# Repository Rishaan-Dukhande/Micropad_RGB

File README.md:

# Rishaan RGB micro hackpad

The RGB micro is a 2 key macropad with a joystick, an OLED Display, and one RGB LED - giving the user multiple ways to change an LED to any color and brightness they want! This serves as the first PCB I have created and is a great introductory project to develop PCB, CAD, and firmware skills for engineering! I created this project to develop these skills and enhance my engineering skills and knowledge. I have used RGBs and there is a color game called hues and cues, and this LED allows you to access a pallet just like the game, but in real life! Features, Images, and steps to recreate this project are listed below.

# Demo

## Features:

* Portable 3D case with openings for components and USB connection
* Seeeduino XIAO SAMD21 controller
* 1 RGB LED for bright color display
* 2 tactile switch buttons for modes and presets
* Small OLED screen that displays the current RGB value in real time.
* Joystick for smooth & dynamic brightness and color control

## How it works

The RGB Micropad is a mini RGB LED controller. The joystick navigates 
a full 360° color wheel — pushing in any direction changes the LED to 
that hue in real time. SW1 toggles between Color mode and Brightness 
mode, while SW2 cycles through 8 color presets. Pressing the joystick 
button activates Saturation mode, letting the user dial between vivid 
and pastel tones and creating a larger array of colors for the LED to
display. The OLED screen shows the current mode, color name, 
RGB values, and brightness percentage at all times.

## PCB

Here's my PCB! Kicad was used to create both the schematic and layout of the pcb.

### Schematic

### PCB

The 1x4 connector on the top is for connecting the Oled Screen (SSD1306 0.91" OLED I2C 128x32) The 1x5 connector on the bottom center of the pcb is for connecting the controling joystick

## Sizes and PCB Info

* Board size: 56.95mm x 68.85mm
* 2 layer PCB
* Designed in KiCad 9.0

## Firmware
Written in CircuitPython. The main.py file enables the user to have the following controls:
* SW1 → Toggle between Color mode and Brightness mode
* SW2 → Cycle through 8 color presets
* Joystick button → Toggle saturation mode on/off
* Joystick X/Y → Navigate color wheel (Color mode) or adjust brightness (Brightness mode)
* OLED display → Shows current mode, color name, RGB values, and brightness %

## BOM:

Here is everything used in the RGB micro hackpad. Note that most of the prices come in sets because components cost the least when they are bought in bulk.

| **Qty** | **Component** | **Note** | **Price** |
|:--:|:--:|:--:|:--:|
| 1 | Seeeduino XIAO SAMD21 | Main processor | [~$5.40](https://www.seeedstudio.com/Seeeduino-XIAO-Arduino-Microcontroller-SAMD21-Cortex-M0+-p-4426.html) |
| 1 | SSD1306 0.91" OLED I2C 128x32 | Displays brightness and color info | [~$7.99](https://www.amazon.com/gp/product/B079BN2J8V/ref=ewc_pr_img_4?smid=A1WZRPJ0MN58A9&th=1) |
| 1 | Analog thumbstick joystick module KY-023 | Joystick control | [~$7.99](https://www.amazon.com/gp/product/B0GWQ6KXYP/ref=ewc_pr_img_3?smid=A3S807LE0L63AP&psc=1) |
| 1 | RGB LED 5mm common cathode | LED that is being controlled | [~$8.99 (100 pack)](https://www.amazon.com/gp/product/B01C3ZZT8W/ref=ewc_pr_img_1?smid=A14FP9XIRL6C1F&th=1) |
| 2 | 10KΩ resistor | Pull up resistors for buttons | [~$8.99 (kit)](https://www.amazon.com/Elegoo-Values-Resistor-Assortment-Compliant/dp/B072BL2VX1) |
| 1 | 220Ω resistor | Red LED pin | [included in resistor kit](https://www.amazon.com/Elegoo-Values-Resistor-Assortment-Compliant/dp/B072BL2VX1) |
| 2 | 47Ω resistor | Green and Blue LED pins | [included in resistor kit](https://www.amazon.com/Elegoo-Values-Resistor-Assortment-Compliant/dp/B072BL2VX1) |
| 2 | Tactile push button 6x6mm | Control modes for joystick control | [~$5.99 (pack)](https://www.amazon.com/gp/product/B07VSNN9S2/ref=ewc_pr_img_2?smid=AJJYA8M5YMCKV&psc=1) |
| 1 | 2.54mm pin header 1x04 | OLED screen connector | [~$6.99 (pack)](https://www.amazon.com/MCIGICM-Header-2-54mm-Arduino-Connector/dp/B07PKKY8BX) |
| 1 | 2.54mm pin header 1x05 | Joystick connector | [included in pack above](https://www.amazon.com/MCIGICM-Header-2-54mm-Arduino-Connector/dp/B07PKKY8BX) |

## Steps to Reproduce

### Parts
Order the parts in the Bill of Materials. These will be soldered on the PCB manually later on (unless specified in JLCPCB)

### PCB Manufacturing
1. Download PCB/gerbers.zip (in PCB folder of repository)
2. Upload to JLCPCB or PCBWay (You can get grants from hackclub if you edit the PCB before upload!)
3. Place the order - remember to pick the least expensive shipping!

### Assembly

1. Solder resistors R1-R5 onto the PCB. Utilize the following resistor values
2. Refer to the table above to read resistor values before incorporating them.
The table below has the resistor values with their placement on the PCB.

| **R#** | **Value** |
|:--:|:--:|
| R1 | 220Ω |
| R2 | 47Ω |
| R3 | 47Ω |
| R4 | 10KΩ |
| R5 | 10KΩ |
  
3. Solder RGB LED into the D1 slot on the PCB
4. Solder tactile switches SW1 and SW2.
5. Solder 5 pin header into the slot for the Joystick
6. Solder 4 pin header into the slot for the OLED screen
7. Solder XIAO SAMD21 on the top left of the board

### Flashing Instructions (Get firmware onto the PCB)
1. Copy or download the firmware as a .ino file and open it in arduino IDE
2. Use a USB-C transfer cable and plug it into the seedunio XAMD 21 and a computer
3. Upload the code using arduino IDE
4. The RGB Micropad will automatically begin to work (it can be plugged in directly to power)

### Verify your RGB Micropad works!
1. Plug in via USB (either computer of any electricity source)
2. OLED should show RGB Micropad splash screen
3. Move joystick to change LED color or brightness (depends on the mode you are on)
4. Press SW1 to toggle between modes!
   Mode 1: Color
   Mode 2: Brightness
5. Press SW2 to cycle through preset colors for LED
6. Press Joystick button to toggle saturation mode (This is an advanced mode for an additional array of colors)

## AI Usage
AI was used during the project as a step-by-step guide. The firmware was also written by AI.

## Devlog
### Session 1 — Schematic Design
The schematic was designed in Kicad. This included the following components:
1) XIAO SAMD21
2) RGB LED
3) Joystick module
4) OLED screen
5) Two tactile buttons

### Session 2 — PCB Layout
Note) This takes about 2 hrs for beginners
1) Layout of all components (If you are replicating, be creative and change locations of components).
2) Added GND copper pour so I don't have to route GND pins of every component
3) Routed the PCB connections between XIAO board and components
4) Created Silkscreen for aesthetics including Hack Club logo and component labels.

### Session 3 - Error with pullup resistors
1) Edited schematic by adding 10KΩ pullup resistors for both tactile switches
2) Used Ohm's law to calculate resistor values for RGB LED pins
   a) Blue and Green pins receive 47Ω resistors
   b) Red pin receives 220Ω resistors
   c) This occurs because they have different voltage requirements in order to power the color
3) Update PCB layout to include the resistors (2hrs).

### Session 4 — Firmware
1) Wrote CircuitPython firmware. This enables the PCB to have the following capabilities:
   a) Implemented color wheel for color mode control
   b) Brightness control from Joystick
   c) Mode navigation button to control both color and brightness with one Joystick
   d) Easily use joystick to change LED characteristics

### Session 5 — Case Design
Designed sandwich mount 3D-case in Fusion 360. The sandwich mount design can be found as the 5th mount in this [Different keyboard mounts](https://www.monsgeek.com/blog/comprehensive-guide-to-keyboard-mounting-styles/) document.

#### Bottom case (1hr)
1) Created bottom case with 0.4 mm clearance for PCB on all sides
2) Added 10mm thick walls all around board and 3.2mm diameter mounting holes
#### Top case (1 hr)
3) Measured placement of components on PCB and created openings
4) Added fillets to strengthen design and make it look good
5) Added project name, author, and hackclub svg logo

### Session 6 - README and Github Polish
1) Reviewed current github
2) Added devlog, images, and project info to the README.

### session 7 - Assembly (3-4 hrs)
1) Soldered components to the PCB
2) Re-designed the case to better fit PCB
3) Created Demo Video

## Extra stuff

I am ready to create more complex hackpads. Through this project, I was able to gain PCB making skills and refine my CAD skills. I am now confident that I can create electronic projects at a much faster pace with the use of these digital designing tools. If you have any project recommendations, please feel free to share them!

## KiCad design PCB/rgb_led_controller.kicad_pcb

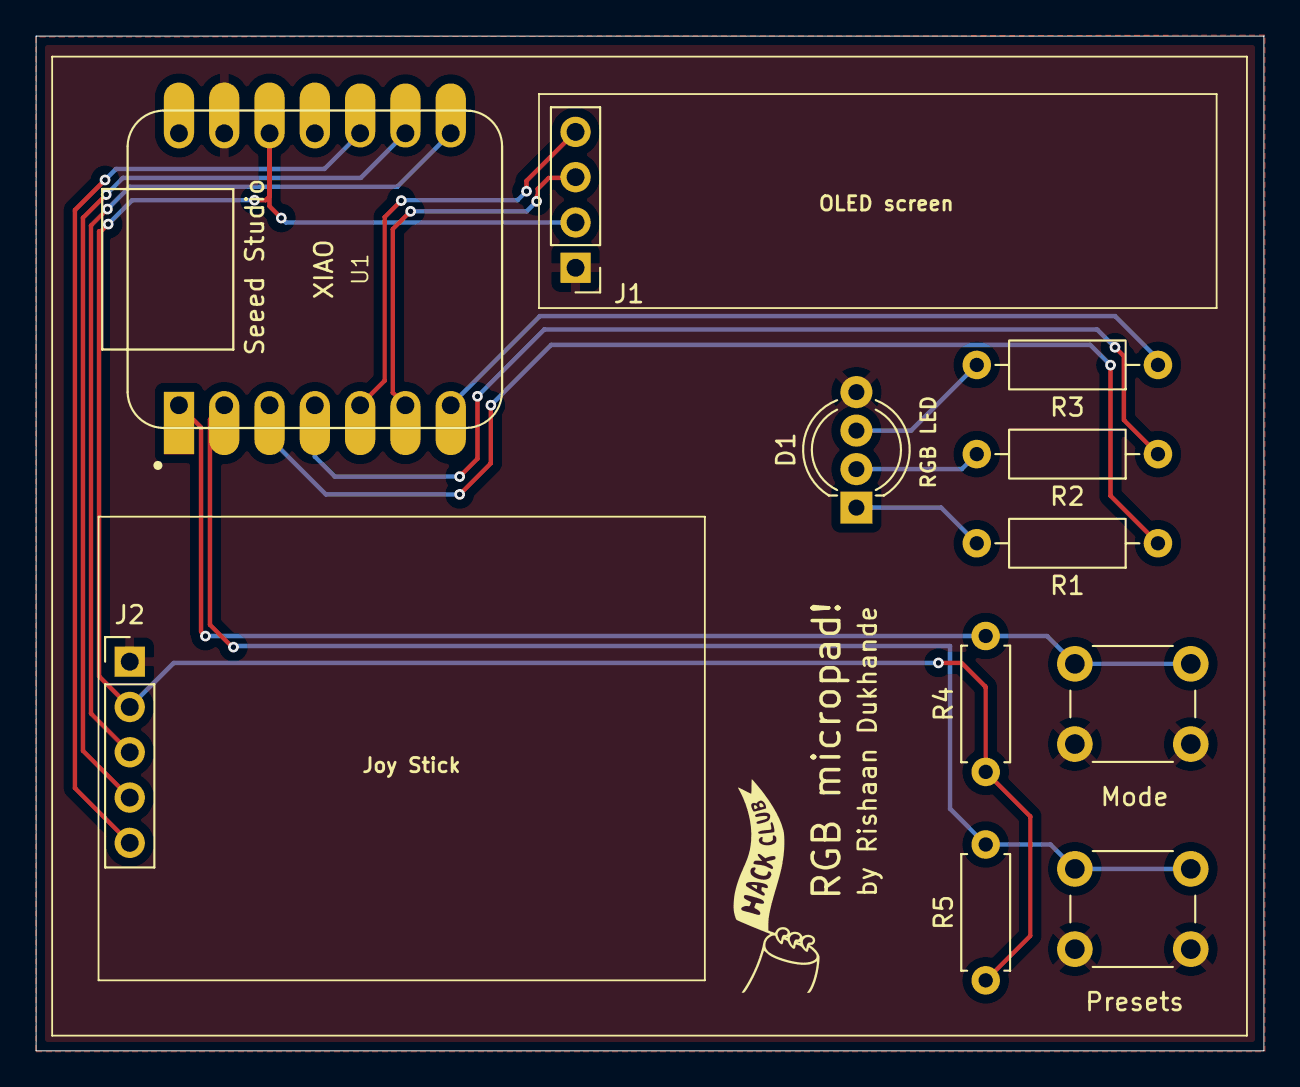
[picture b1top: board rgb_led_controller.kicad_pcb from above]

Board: 2 copper layers, 68.8 x 56.9 mm, 12 parts (0 on the bottom side), 15 nets.

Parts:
D1: LED_RGB; LED_D5.0mm-4_RGB_Wide_Pins
J1: Conn_01x04; PinHeader_1x04_P2.54mm_Vertical
J2: Conn_01x05; PinHeader_1x05_P2.54mm_Vertical
Mode: SW_Push; SW_PUSH_6mm
Presets: SW_Push; SW_PUSH_6mm
R1: 220; R_Axial_DIN0207_L6.3mm_D2.5mm_P10.16mm_Horizontal
R2, R3: 47; R_Axial_DIN0207_L6.3mm_D2.5mm_P10.16mm_Horizontal
R4, R5: 10K; R_Axial_DIN0207_L6.3mm_D2.5mm_P7.62mm_Horizontal
U1: MOUDLE-SEEEDUINO-XIAO; XIAO-Generic-Hybrid-14P-2.54-21X17.8MM
logo: LOGO

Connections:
+3V3: J1.2, J2.2, R4.1, R5.1, U1.12 (3V3)
/JOY_X: J2.3, U1.8 (PB09_A7_D7_RX)
/JOY_Y: J2.4, U1.9 (PA7_A8_D8_SCK)
/LED_B: D1.3 (BK), R3.2
/LED_G: D1.2 (GK), R2.2
/LED_R: D1.1 (RK), R1.2
/SCL: J1.3, U1.6 (PA9_A5_D5_SCL)
/SDA: J1.4, U1.5 (PA8_A4_D4_SDA)
/SW: J2.5, U1.10 (PA5_A9_D9_MISO)
GND: D1.4 (BA), J1.1, J2.1, Mode.2, Presets.2, U1.13 (GND)
unnamed: Mode.1, R4.2, U1.1 (PA02_A0_D0)
unnamed: Presets.1, R5.2, U1.2 (PA4_A1_D1)
unnamed: R1.1, U1.3 (PA10_A2_D2)
unnamed: R2.1, U1.4 (PA11_A3_D3)
unnamed: R3.1, U1.7 (PB08_A6_D6_TX)

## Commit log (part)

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2026-04-01 Create files
2026-04-01 Create folder
2026-04-01 Create circutpython_firmware
2026-04-01 Create cad
2026-04-01 Enhance README with functionality details and PCB info
    Added a section explaining how the RGB micro works and updated the PCB description to clarify the use of KiCad.
2026-04-01 Update README to remove OLED display specification
    Removed mention of the 128x32 OLED Display from the README.
2026-05-25 Initial PCB commit - RGB Micropad complete
2026-05-25 RGB micropad update - new design with module errors fixed
2026-05-25 Reorganized repo for Blueprint submission
2026-05-25 Cleaned root - removed loose files, added missing folders
2026-05-25 Added Images folder
2026-05-25 Add README for RGBmicro hackpad project
    Added detailed information about the RGBmicro hackpad, including features, operation, PCB details, sizes, firmware, BOM, and future plans.
2026-05-26 Refactor README.md for clarity and image inclusion
    Updated README.md to improve formatting and add images.
2026-05-26 Update README.md with project details
2026-05-26 Added Saturation + comments
    Updated firmware to include saturation mode and improved OLED display functionality.
2026-06-04 Added complete Fusion 360 case - top plate and bottom case with branding
2026-06-04 Enhance README with BOM, assembly, and devlog
    Updated README.md to include additional BOM details, steps to reproduce, and devlog entries.
2026-06-05 Added schematic and PCB layout PDFs to Images folder
2026-06-05 Updated silkscreen labels, re-exported Gerbers, fixed README
2026-06-06 Added full assembly screenshot, f3z source file, BOM.csv
2026-06-06 Resistor value chart added to BOM
2026-06-06 Removed .DS_Store files, added gitignore
2026-06-06 Cleaned up junk files, added gitignore, added purpose to readME
2026-06-06 Removed remaining autosave lock file
2026-06-08 Revise README for RGB micro hackpad project
    Updated README.md to include project details, features, and assembly instructions for the RGB micro hackpad.
2026-06-10 Add combined STEP file with OLED and joystick models
2026-06-12 Add journal images
2026-06-12 Fix silkscreen inaccuracies
